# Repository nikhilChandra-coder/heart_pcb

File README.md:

PCB 3D model

Circuit Schematic

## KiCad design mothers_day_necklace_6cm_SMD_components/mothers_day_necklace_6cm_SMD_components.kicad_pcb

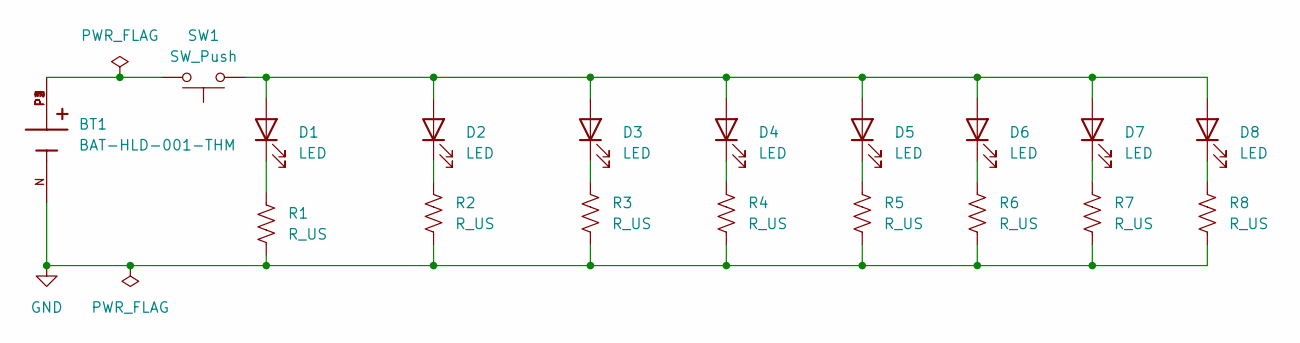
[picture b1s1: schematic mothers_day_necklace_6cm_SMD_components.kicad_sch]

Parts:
BT1: BAT-HLD-001-THM; BAT_BAT-HLD-001-THM
D1, D2, D3, D4, D5, D6, D7, D8: LED; LED_0805_2012Metric
R1, R2, R3, R4, R5, R6, R7, R8: R_US; R_0805_2012Metric
SW1: SW_Push; SW_Tactile_SPST_NO_Straight_CK_PTS636Sx25SMTRLFS

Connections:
GND: BT1.N, R1.2, R2.2, R3.2, R4.2, R5.2, R6.2, R7.2, R8.2
unnamed: BT1.P1, BT1.P2, BT1.P3, BT1.P4, SW1.2
unnamed: D1.2 (A), D2.2 (A), D3.2 (A), D4.2 (A), D5.2 (A), D6.2 (A), D7.2 (A), D8.2 (A), SW1.1
unnamed: D1.1 (K), R1.1
unnamed: D2.1 (K), R2.1
unnamed: D3.1 (K), R3.1
unnamed: D4.1 (K), R4.1
unnamed: D5.1 (K), R5.1
unnamed: D6.1 (K), R6.1
unnamed: D7.1 (K), R7.1
unnamed: D8.1 (K), R8.1

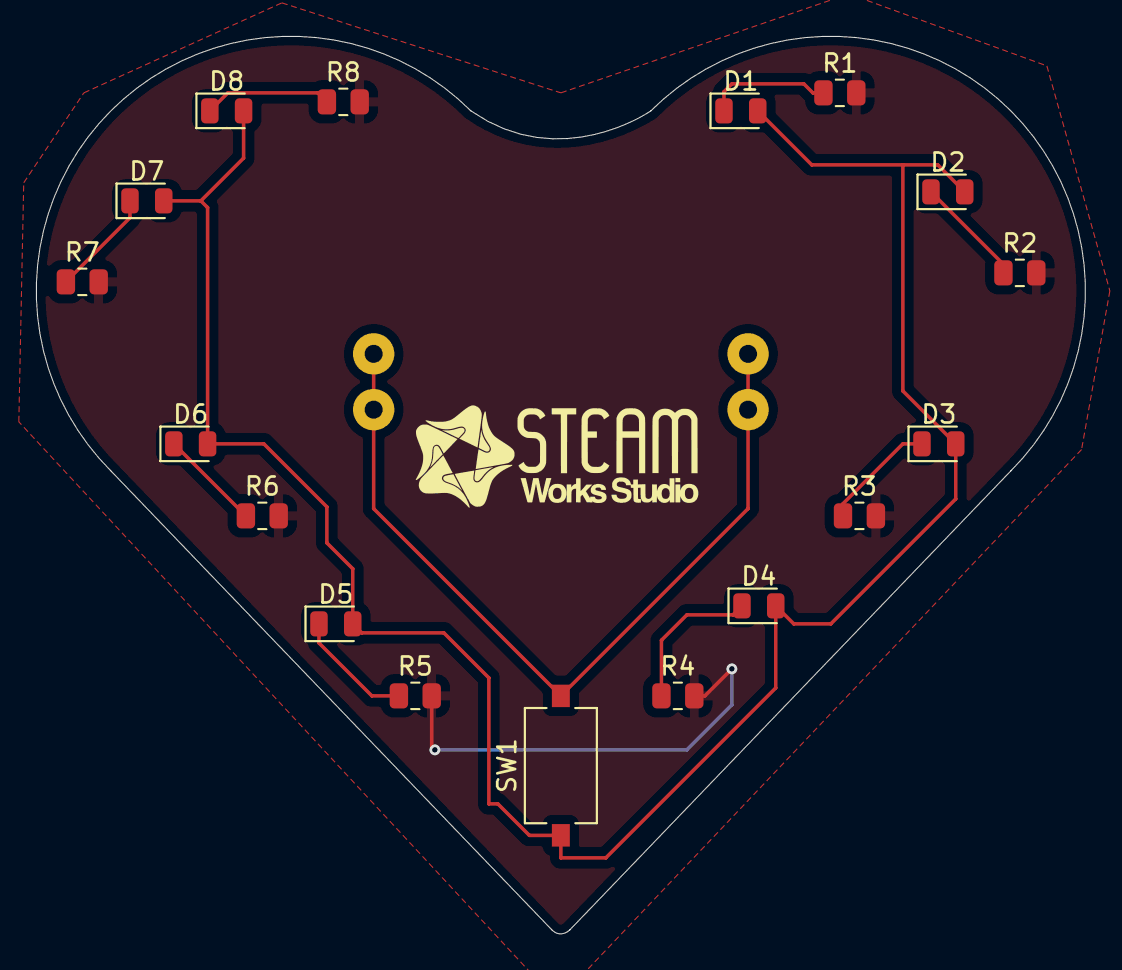
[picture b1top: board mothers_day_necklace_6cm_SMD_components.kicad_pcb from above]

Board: 2 copper layers, 58.3 x 49.9 mm, 18 parts (1 on the bottom side), 11 nets.

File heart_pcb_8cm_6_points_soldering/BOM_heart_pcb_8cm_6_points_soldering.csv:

Comment,Designator,Footprint,Quantity,JLCPCB Part #?optional?
SW_Push,SW1,SW_PUSH_6mm,1,
BAT-HLD-001-THM,BT1,BAT_BAT-HLD-001-THM,1,
470,"R2,R3,R1",R_Axial_DIN0207_L6.3mm_D2.5mm_P10.16mm_Horizontal,3,

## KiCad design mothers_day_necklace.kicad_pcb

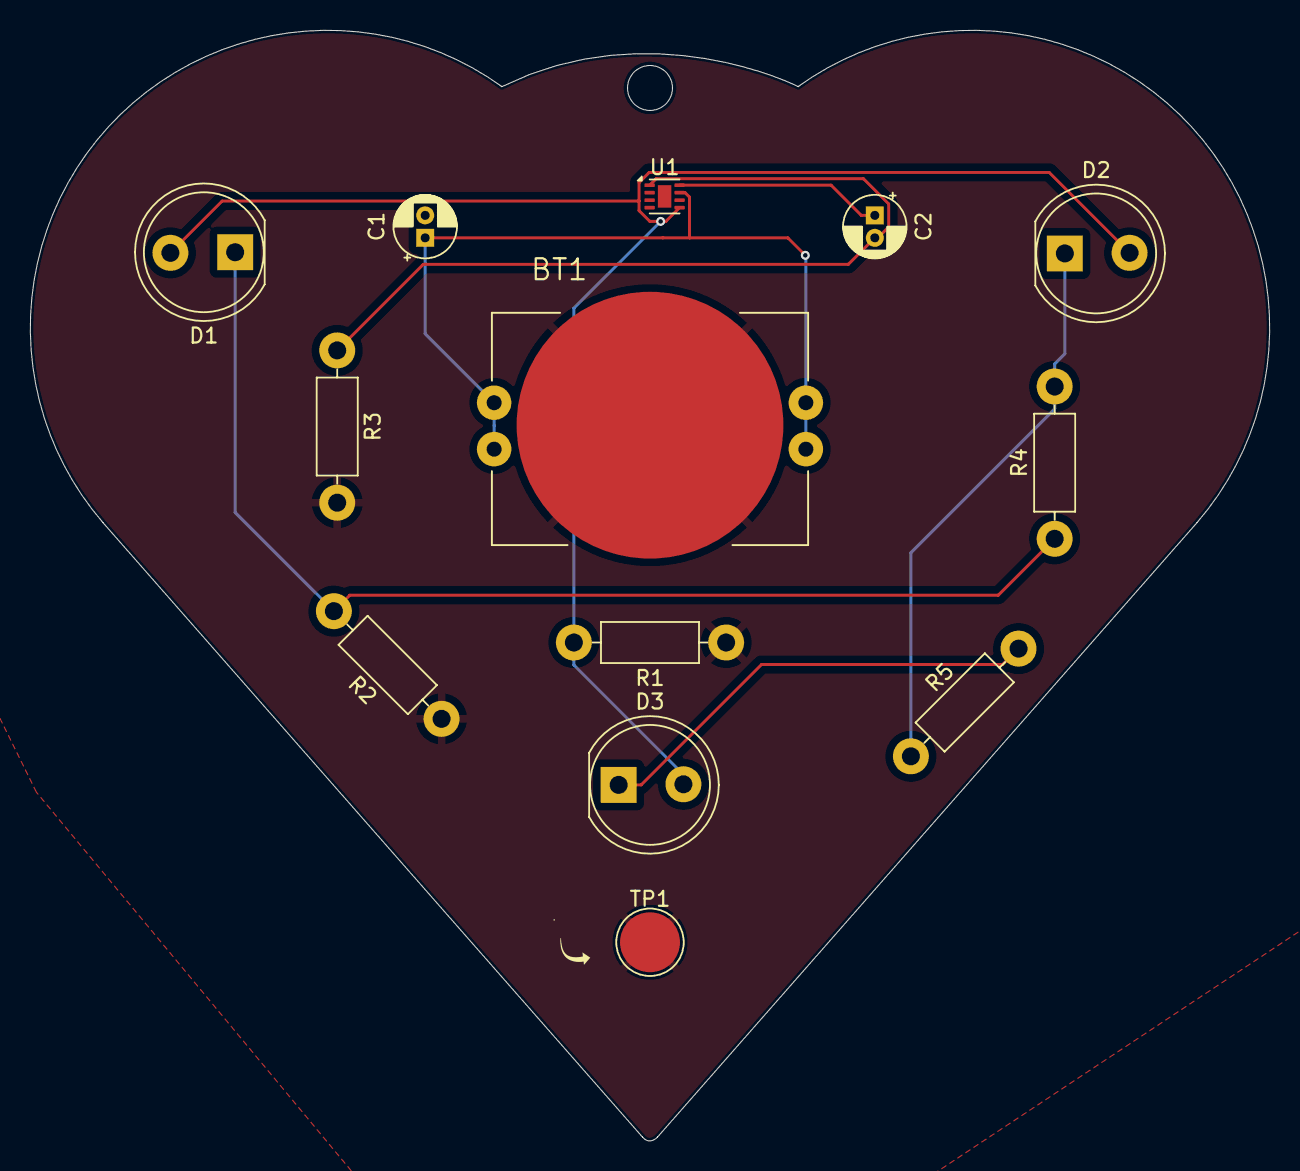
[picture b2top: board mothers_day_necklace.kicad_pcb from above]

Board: 2 copper layers, 82.7 x 74.1 mm, 14 parts (0 on the bottom side), 8 nets.

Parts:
BT1: BAT-HLD-001-THM; BAT_BAT-HLD-001-THM
C1: 0.1uF; CP_Radial_D4.0mm_P1.50mm
C2: 6.8nF; CP_Radial_D4.0mm_P1.50mm
D1, D2, D3: LED; wider LED_D8.0mm
H1: MountingHole; MountingHole_3mm
R1: 100k; bigpad-no-cutout-R_Axial_DIN0207_L6.3mm_D2.5mm_P10.16mm_Hor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
R2, R4, R5: 1k; bigpad-no-cutout-R_Axial_DIN0207_L6.3mm_D2.5mm_P10.16mm_Hor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
R3: 4.7k; bigpad-no-cutout-R_Axial_DIN0207_L6.3mm_D2.5mm_P10.16mm_Hor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
TP1: TestPoint; TestPoint_Pad_D4.0mm
U1: AT42QT1012-M; DFN-8-1EP_2x2mm_P0.5mm_EP0.9x1.5mm

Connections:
GND: BT1.N, C1.2, R1.1, R2.1, R3.2, TP1.1
unnamed: D1.2 (A), D2.2 (A), D3.2 (A), R1.2, U1.5 (OUT)
unnamed: D1.1 (K), R2.2, R4.1
unnamed: D2.1 (K), R4.2, R5.1
unnamed: D3.1 (K), R5.2
unnamed: C2.1, U1.8 (SNS)
unnamed: C2.2, R3.1, U1.1 (SNSK)
VDD: BT1.P1, BT1.P2, BT1.P3, BT1.P4, C1.1, U1.7 (VDD)

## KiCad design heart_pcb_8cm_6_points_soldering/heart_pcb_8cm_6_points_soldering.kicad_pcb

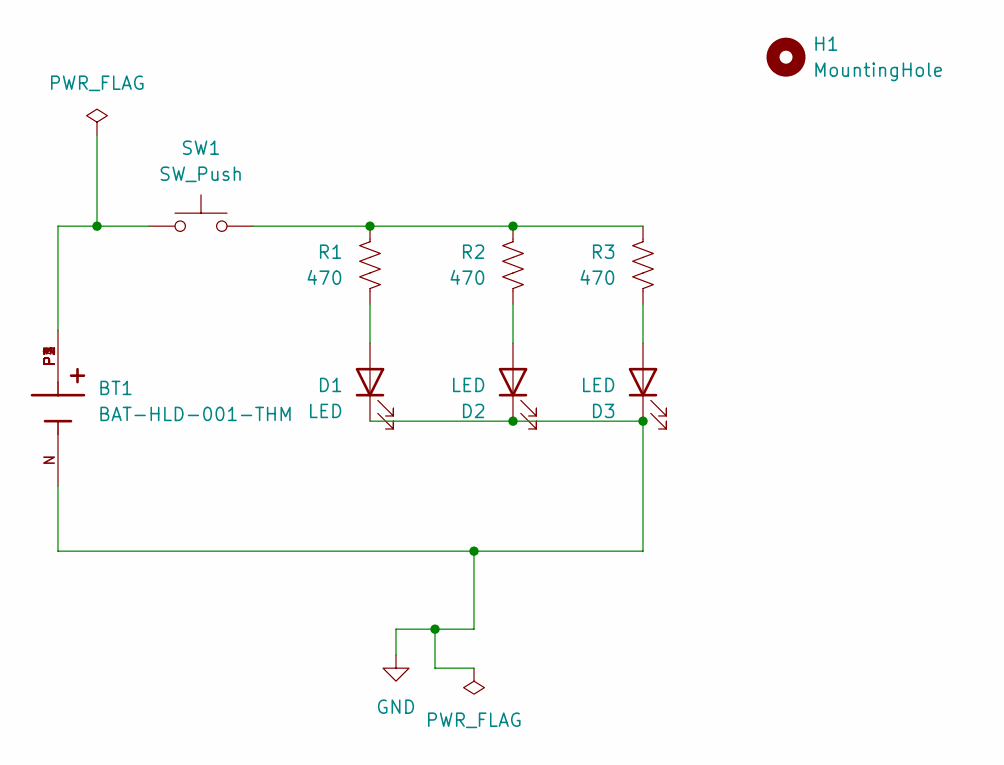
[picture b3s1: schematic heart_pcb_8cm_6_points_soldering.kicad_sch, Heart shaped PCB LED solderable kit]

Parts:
BT1: BAT-HLD-001-THM; BAT_BAT-HLD-001-THM
D1, D2, D3: LED; wider LED_D8.0mm
H1: MountingHole; MountingHole_5mm
R1, R2, R3: 470; R_Axial_DIN0207_L6.3mm_D2.5mm_P10.16mm_Horizontal
SW1: SW_Push; SW_PUSH_6mm

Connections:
GND: BT1.N, D1.1 (K), D2.1 (K), D3.1 (K)
unnamed: BT1.P1, BT1.P2, BT1.P3, BT1.P4, SW1.1
unnamed: D1.2 (A), R1.1
unnamed: D2.2 (A), R2.1
unnamed: D3.2 (A), R3.1
unnamed: R1.2, R2.2, R3.2, SW1.2

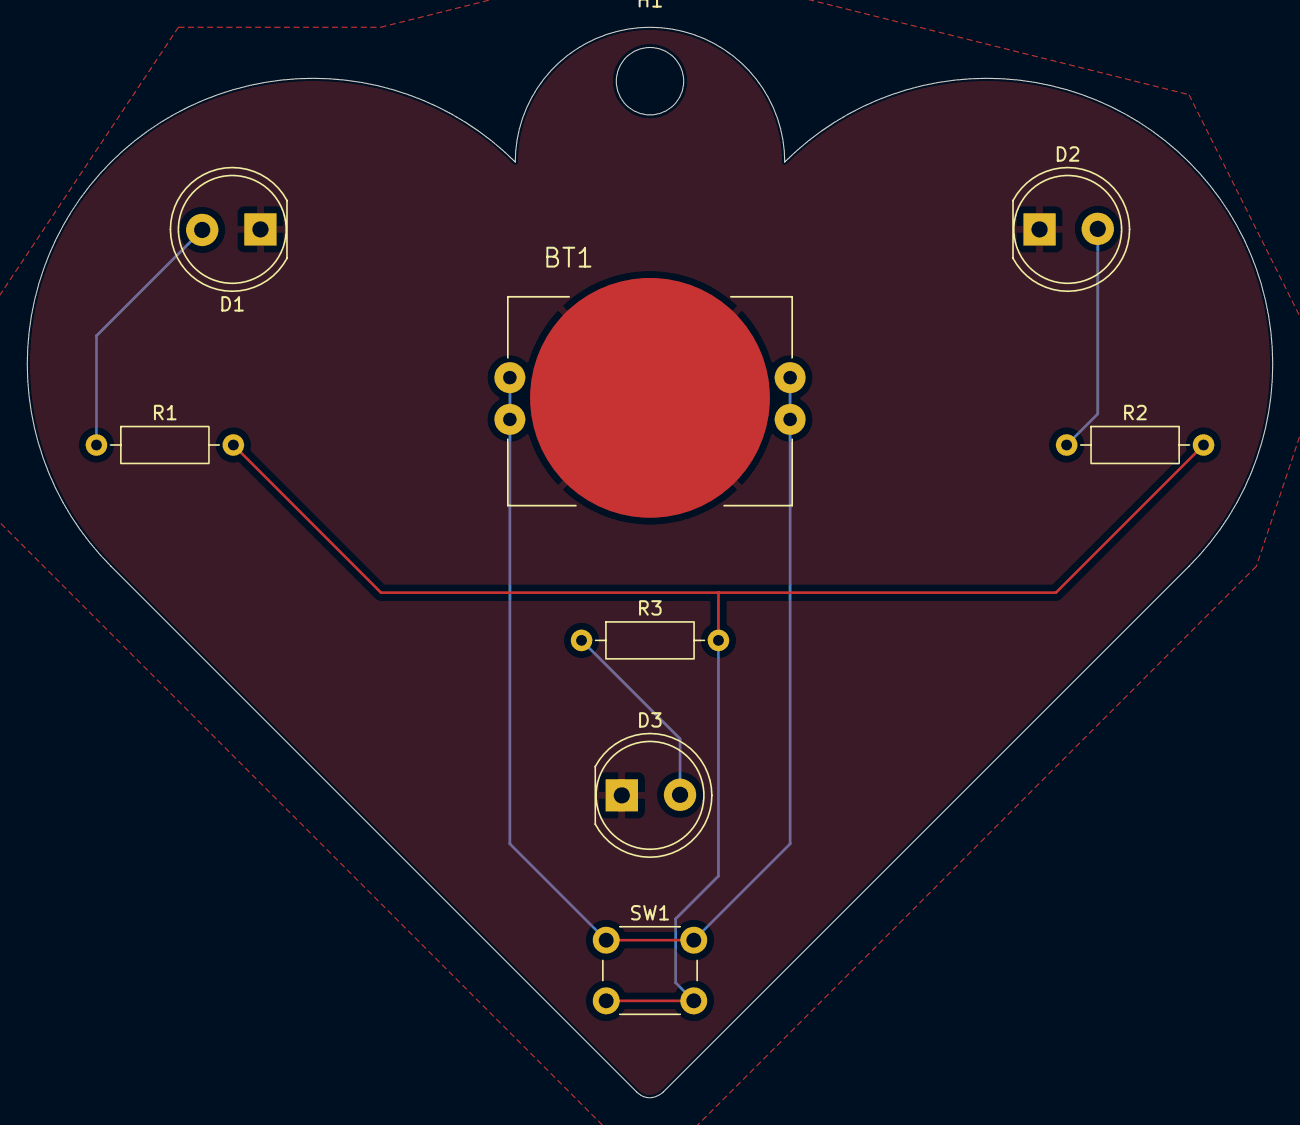
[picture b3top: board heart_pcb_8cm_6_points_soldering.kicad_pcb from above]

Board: 2 copper layers, 92.4 x 79.4 mm, 9 parts (0 on the bottom side), 6 nets.

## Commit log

2026-02-19 heart pcb initial commit
2026-02-19 removing gerbers
2026-02-19 removing gerbers for real
2026-02-19 Final cleanup: Remove Gerbers from repository tracking
2026-02-19 Add image to README.md
2026-03-18 Add PCB 3D model and circuit schematic images to README
